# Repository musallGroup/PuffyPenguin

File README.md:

# PuffyPengiun

Multimodal rate discriminaton behavioral task for mice.

## Description of the setup

This should show a labeled picture of the setup. 

## Data saving and automatic copy

This should say what gets saved where and what is automatically copied and when. 

The TouchShaker teensy module reports lick and handle touch times, these get communicated and logged by Bpod.

### SessionData.RawEvents

Event list correspondence :

| TouchShaker byte | Event |
|------------------|-------|
| TouchShaker1_1 | left_spout_touch |
| TouchShaker1_2 | right_spout_touch |
| TouchShaker1_3 | left_spout_release |
| TouchShaker1_4 | right_spout_release |
| TouchShaker1_5 | left_handle_touch |
| TouchShaker1_6 | right_handle_touch |
| TouchShaker1_7 | both_handle_touch |
| TouchShaker1_8 | left_handle_release |
| TouchShaker1_9 | right_handle_release |
| TouchShaker1_14 | acknowledge |
| TouchShaker1_15 | error |

State list correspondence:

## Settings and description

Settings can be set from Bpod (mat files in Bpod Local/Settings).
Default settings are in SpatialSparrow.m

Settings for `training control`:

| Setting | Default | Description |
|---------|---------|-------------|
| SubjectName | | Name of the mouse |
| RewardedModality | AudioVisual |'Vision', 'Audio', Somatossensory, 'AudioVisual', 'Mixed' |
| leftRewardVolume | 2 ul | Amount of water per left reward |
| rightRewardVolume | 2 ul | Amount of water per right reward |
| AutoReward | OFF | Pre-load rewarded spout |
| TrainingMode | OFF | Move spouts to the correct side |
| autoRewardVision | 1 | Fraction of self-performed trials (Vision) |
| autoRewardAudio | 1 | Fraction of self-performed trials (Auditory) |
| autoRewardPiezo | 1 | Fraction of self-performed trials (Somatossensory) |
| autoRewardMixed | 1 | Fraction of self-performed trials (Mixed) |
| LeverSound | true | Play a sound when the mouse touches the handles |
| RegularStim | false | Produce regular stimuli sequences |
| biasSeqLength | 3 | nr of trials on one side after which the oposite side is switched with 50% probability |

Settings for `trial timing` :

| Setting | Default | Description |
|---------|---------|-------------|
| preStimDelay | 1 (s) | time on handle before stimuli presentation |
| StimDuration | 1 (s) | duration of the stimulus |
| happyTime | 0.5 (s) | duration of the last state (gives time to collect reward) |
| varStimDur | 0 (s) | variable stim duration (StimDuration + varStimDur) is the actual stim duration |
| optoDur | 0.5 (s) | duration of the optogenetics stimuli |
| optoRmp | 0.2 (s) | duration of the optogenetics ramp down (optoDur = 0.5 and optoRamp = 0.2 makes a 500ms stimulus that ramps down after 300ms) ??????? |
| minITI | 1 (s) | min inter trial interval (additional) |
| maxITI | 2 (s) | max inter trial interval (additional) |
| ITIlambda | 10 (AU) | bariability between minITI and maxITI. High lambda -> closer to minITI |
| WaitingTime | 1 (s) | minimum waiting time before a response can be made, early licks are ignored |
| TimeToChoose | 3 (s) | how long to wait for choice report |
| TimeToConfirm | 0.5 (s) | how long to wait for a 2nd (confirmation) lick |
| Timeout | 3 (s) | timeout to punish wrong responses |
| LeverWait | 10 (s) | time to wait for handle grasp |
| MoveLever | TRUE | move levers or not (set to FALSE during habituation)|
| UseBothLevers | FALSE | Whether both handles need to be touched to initiate trials |
| WaitBeforeLever | 1 (s) | Wait time before handles are moved in after trial onset|

Settings for `stimuli parameters` :

| Setting | Default | Description |
|---------|---------|-------------|
| TargRate  | 10 (Hz) | Rate of the target sequence |
| ProbRight  | 0.5 | Fraction of targets on the right |
| DistFractions  | 0  | Distractor pulses (fraction of the target sequence). Can be a scalar [0-1] or a vector |
| DistProb  | 0  | Probability of presenting a distractor |
| TestModality  | 0  | Modality to be used with discrimination (1=vis, 2=aud, 4=ss). Zero is inactive. Other values are detection only |
| BinSize  | 50 (ms) | Stimuli refractory period (min interval between pulses) |
| StimCoherence  | TRUE | Determines whether multisensory stimuli are correlated | 
| UseNoise  | FALSE | Use noise burst (TRUE) of clicks (FALSE) as auditory stimuli |
| varStimOn  | [0 0.125 0.25] (s) | Variable onset time for stimulus after lever grab in s. This can be a vector of values. Have to be 0 and higher. |
| StimGap  | 0 (s) | Duration of the gap in the middle of stimulus presentation in s; if >0 the stim duration is of stimDuration*2 + stimGap long |
| DecisionGap  | [0.3 1.5] (s) | Range of the interval between the stimulus and the decision period |
| BeepDuration  | 20 (ms) | Beep (auditory) duration |
| StimLoudness  | 0.5 | Strength of auditory stimuli |
| FlashDuration  | 20 (ms) | Flash (visual) duration |
| StimBrightness  | 20  | Brightness of flashes. Multiplier of the base frequency, default is 100Hz (????) |
| BuzzDuration  | 20 (ms) | Buzz (somatossensory) duration |
| BuzzStrength  | 1  | Strength of buzzes |
| ProbAudio  | 0  | Probability of presenting an auditory-only trial (for multimodal) |
| ProbVisual  | 0  | Probability of presenting a visual-only trial (for multimodal) |
| ProbPiezo  | 0  | Probability of presenting a somatossensory-only trial (for multimodal) |
| sRate  | 20000  | Sampling rate of the AnalogOutput module |
| PunishSoundDur  | 0 (s)  | Duration of the white noise punishment sound |
| optoProb  | 0  | Fraction of optogenetics trials |
| optoTimes  | Stimulus/Delay | Part of the trial where optogenetic stimulus should be presented |
| optoRight  | 0.5  | Probability for occurence of an optogenetic stimulus on the right |
| optoBoth  | 1  | Probability for occurence of an optogenetic stimulus on both sides. This comes after determining a single HS target ??? |
| optoPower  | 5  | Fraction of optogenetics stimuli |

Settings for `hardware control and sync` :

| Setting | Default | Description |
|---------|---------|-------------|
| SpoutSpeed | 25 (ms) | Duration of spout movement |
| rMaxSpoutIn | 30 | Right spout inner position (value between 0 and 100) |
| lMaxSpoutIn | 30 | Left spout outer position (value between 0 and 100) |
| spoutOffset | 10 | Distance from inner spout position |
| lOuterLim | 3.5 | Left spout outer position (value between 0 and 100) |
| LeverSpeed | 150 (ms) | Duration of handle movement (ms) |
| LeverIn | 20 | Inner position of the handles |
| LeverOut | 0 | Position of handle out of reach |
| TouchThresh| 5 (SDUs) | Threshold for capacitive touch lines |
| WaitForCam  | false  | Trials wait for a camera trigger to start. |

To check: rInnerLim, lInnerLim, rOuterLim, lOuterLim

Settings for `paths and data copy` :
| Setting | Default | Description |
|---------|---------|-------------|
| widefieldPath | ... | path to widefield data on server |
| serverPath |  ... | path to behavioral data on server |
| videoDrive | C: | path to behavioral data on server |
| bonsaiEXE | ... | path to bonsai.exe  |
| bonsaiParadim | ... | path to the bonsai workflow ('' to skip bonsai)  |
| labcamsAddress | localhost:9999 | address to connect to labcams for video acquisition (leave empty to skip) |
| wavePort | COM18 | COM port of the AnalogOutput Module |

`Plot` settings:
| Variable | Default | Description |
|----------|---------|-------------|
| PerformanceSwitch| Performed | Show performance over all trials or only self-performed trials |
| DoFit| false | Show curve fitting in the performance plot |
| modSelector| Combined | Which data to show in the performance plot |

Operational variables:
| Variable | Default | Description |
|----------|---------|-------------|
| SaveSettings | false | Saves the current settings |
| AdjustSpouts | 0 | Pause for spout adjustment |
| StartTime | ? | Start time of the current session |
| cTrial |  | Number of the current trial |
| runTime |  | Duration of the current session |
| servoPos | [0 0] | position of left and right spout, relative to their inner limit. these values will be changed by anti-bias correction to correct spout position |

## Instalation and build instructions

Clone the repository to Bpod Local/Protocols. If you make changes; create a branch and remember to commit changes regularly.

Build instructions coming here soon.

### Video

There are 2 options for recording video with SpatialSparrow: using [Bonsai](https://bonsai-rx.org/introduction) or using [labcams](https://bitbucket.org/jpcouto/labcams). This readme should show you how to sync the cameras to the BPod (work in progress).

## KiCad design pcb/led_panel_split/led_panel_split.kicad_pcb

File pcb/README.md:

# Printed Circuit Boards and build instructions

## Changing the printed circuit boards

The LED panel PCB was created fully in KiCAD because it is opensource. We used SeeedStudio to manufacture the circuit boards. A list of components is linked here.

### Generating gerber and drill files from KiCAD

 To get the PCB printed you may want to regenerate the GERBER and drill files.

This is how to do it to print in seeedstudio:

 - go to *File* -> *Plot*
 - select the **output directory**, plot format: **Gerber**
 - select layers: **F.Cu; B.Cu; B.SilkS;F.SilkS;B.Mask;F.Mask;Edge.Cuts**
 - select options: **Plot footprint values**; **Plot footprint references**; **Exclude PCB edge layer from other layers**; **Default line width (mm): 0.1**
 - gerber options: **Use protel filename extensions** and Format: 4.6 (unit mm)
 - clicking Plot will generate the Gerber files; to gererate drill files click *drill file*
 - Select **Merge PTH and NPTH into one file.** Unit: **milimeters** ; **suppress leading zeros** ; **PostScript** format; **Absolute origin**.

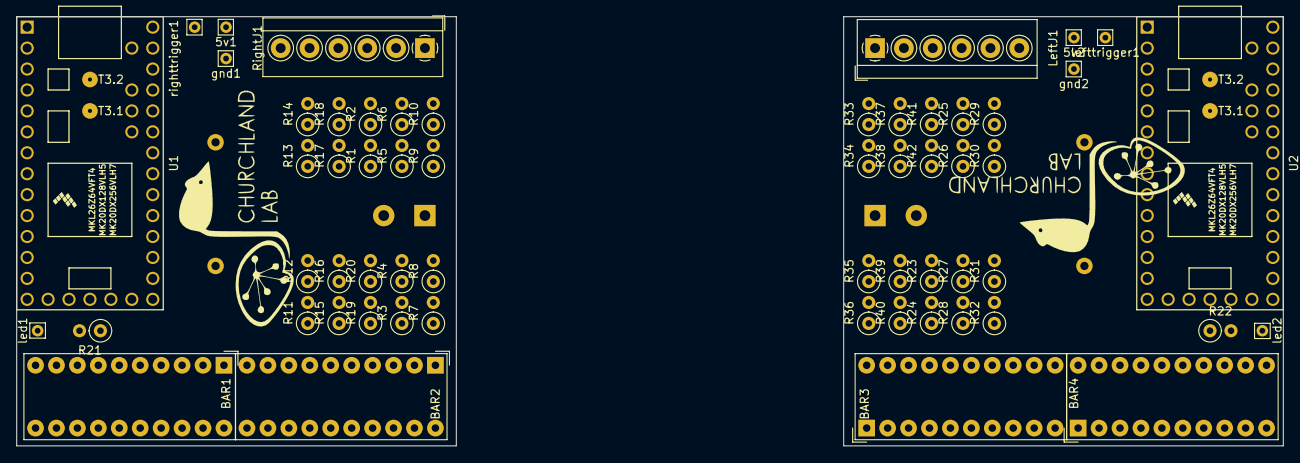
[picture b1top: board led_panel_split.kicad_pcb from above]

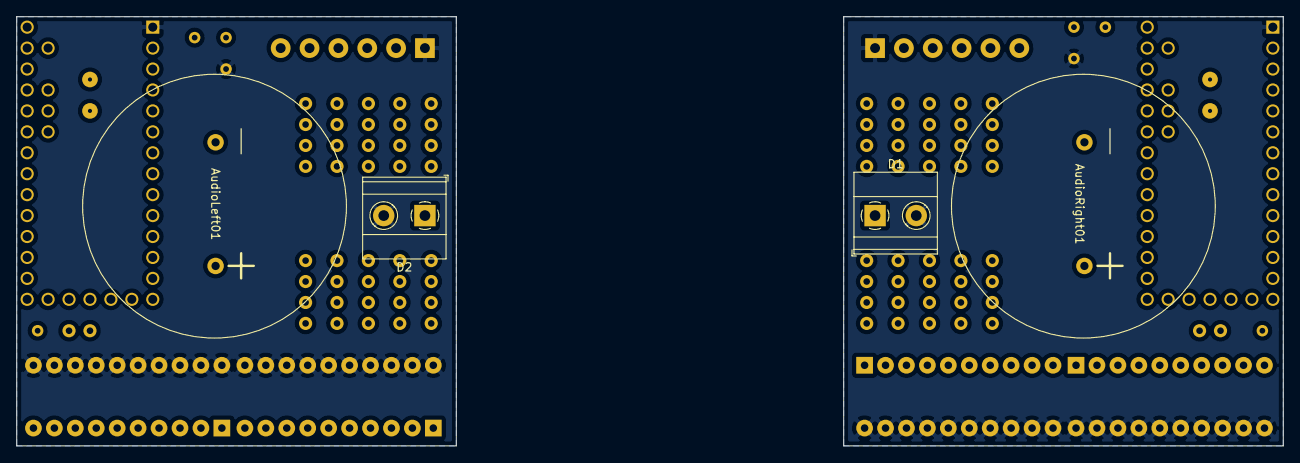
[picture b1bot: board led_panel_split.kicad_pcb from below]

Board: 2 copper layers, 153.7 x 52.1 mm, 64 parts (4 on the bottom side), 92 nets, no tracks yet.

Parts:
5v1, 5v2: 5V; Pin_D0.7mm_L6.5mm_W1.8mm_FlatFork
AudioLeft01: Audio left; speaker
AudioRight01: Audio right; speaker
BAR1, BAR2, BAR3, BAR4: HDSP-4830_2; HDSP-4830
D1, D2: LED; TerminalBlock_Phoenix_MKDS-1,5-2_1x02_P5.00mm_Horizontal
G1, G2: LOGO; churchland_lab_logo
LeftJ1: Left screw terminal; TerminalBlock_4Ucon_1x06_P3.50mm_Horizontal
R1, R2, R3, R4, R5, R6, R7, R8, R9, R10, R11, R12, R13, R14, R15, R16, R17, R18, R19, R20, R21, R22, R23, R24, R25, R26, R27, R28, R29, R30, R31, R32, R33, R34, R35, R36, R37, R38, R39, R40, R41, R42: R; R_Axial_DIN0207_L6.3mm_D2.5mm_P2.54mm_Vertical
RightJ1: Right screw terminal; TerminalBlock_4Ucon_1x06_P3.50mm_Horizontal
U1, U2: Teensy3.2; Teensy30_31_32_LC
gnd1, gnd2: GND; Pin_D0.7mm_L6.5mm_W1.8mm_FlatFork
led1: LED1 test; Pin_D0.7mm_L6.5mm_W1.8mm_FlatFork
led2: LED2 test; Pin_D0.7mm_L6.5mm_W1.8mm_FlatFork
lefttrigger1: left trigger; Pin_D0.7mm_L6.5mm_W1.8mm_FlatFork
righttrigger1: right trigger; Pin_D0.7mm_L6.5mm_W1.8mm_FlatFork

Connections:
+5V: 5v1.1, 5v2.1, LeftJ1.2, RightJ1.2, U1.33, U2.33
GND: BAR1.11, BAR1.12, BAR1.13, BAR1.14, BAR1.15, BAR1.16, BAR1.17, BAR1.18, BAR1.19, BAR1.20, BAR2.11, BAR2.12, BAR2.13, BAR2.14, BAR2.15, BAR2.16, BAR2.17, BAR2.18, BAR2.19, BAR2.20, BAR3.11, BAR3.12, BAR3.13, BAR3.14, BAR3.15, BAR3.16, BAR3.17, BAR3.18, BAR3.19, BAR3.20, BAR4.11, BAR4.12, BAR4.13, BAR4.14, BAR4.15, BAR4.16, BAR4.17, BAR4.18, BAR4.19, BAR4.20, D1.2, D2.2, LeftJ1.1, RightJ1.1, U1.1, U2.1, gnd1.1, gnd2.1
unnamed: AudioLeft01.1, LeftJ1.5
unnamed: AudioLeft01.2, LeftJ1.6
unnamed: AudioRight01.1, RightJ1.5
unnamed: AudioRight01.2, RightJ1.6
unnamed: BAR1.1, R20.2
unnamed: BAR1.2, R19.2
unnamed: BAR1.3, R18.2
unnamed: BAR1.4, R17.2
unnamed: BAR1.5, R16.2
unnamed: BAR1.6, R15.2
unnamed: BAR1.7, R14.2
unnamed: BAR1.8, R13.2
unnamed: BAR1.9, R12.2
unnamed: BAR1.10, R11.2
unnamed: BAR2.1, R10.2
unnamed: BAR2.2, R9.2
unnamed: BAR2.3, R8.2
unnamed: BAR2.4, R7.2
unnamed: BAR2.5, R6.2
unnamed: BAR2.6, R5.2
unnamed: BAR2.7, R4.2
unnamed: BAR2.8, R3.2
unnamed: BAR2.9, R2.2
unnamed: BAR2.10, R1.2
unnamed: BAR3.1, R33.2
unnamed: BAR3.2, R34.2
unnamed: BAR3.3, R35.2
unnamed: BAR3.4, R36.2
unnamed: BAR3.5, R37.2
unnamed: BAR3.6, R38.2
unnamed: BAR3.7, R39.2
unnamed: BAR3.8, R40.2
unnamed: BAR3.9, R41.2
unnamed: BAR3.10, R42.2
unnamed: BAR4.1, R23.2
unnamed: BAR4.2, R24.2
unnamed: BAR4.3, R25.2
unnamed: BAR4.4, R26.2
unnamed: BAR4.5, R27.2
unnamed: BAR4.6, R28.2
unnamed: BAR4.7, R29.2
unnamed: BAR4.8, R30.2
unnamed: BAR4.9, R31.2
unnamed: BAR4.10, R32.2
unnamed: D1.1, R21.2
unnamed: D2.1, R22.2
unnamed: LeftJ1.3, R22.1, led2.1
unnamed: LeftJ1.4, U2.30, lefttrigger1.1
unnamed: R1.1, U1.12
unnamed: R2.1, U1.13
unnamed: R3.1, U1.14
unnamed: R4.1, U1.20
unnamed: R5.1, U1.21
unnamed: R6.1, U1.22
unnamed: R7.1, U1.23
unnamed: R8.1, U1.24
unnamed: R9.1, U1.25
unnamed: R10.1, U1.26
unnamed: R11.1, U1.2
unnamed: R12.1, U1.3
unnamed: R13.1, U1.4
unnamed: R14.1, U1.5
unnamed: R15.1, U1.6
unnamed: R16.1, U1.7
unnamed: R17.1, U1.8
unnamed: R18.1, U1.9
unnamed: R19.1, U1.10
unnamed: R20.1, U1.11
unnamed: R21.1, RightJ1.3, led1.1
unnamed: R23.1, U2.11
unnamed: R24.1, U2.10
unnamed: R25.1, U2.9
unnamed: R26.1, U2.8
unnamed: R27.1, U2.7
unnamed: R28.1, U2.6
unnamed: R29.1, U2.5
unnamed: R30.1, U2.4
unnamed: R31.1, U2.3
unnamed: R32.1, U2.2
unnamed: R33.1, U2.26
unnamed: R34.1, U2.25
unnamed: R35.1, U2.24
unnamed: R36.1, U2.23
unnamed: R37.1, U2.22
unnamed: R38.1, U2.21
unnamed: R39.1, U2.20
unnamed: R40.1, U2.14
unnamed: R41.1, U2.13
unnamed: R42.1, U2.12
unnamed: RightJ1.4, U1.30, righttrigger1.1

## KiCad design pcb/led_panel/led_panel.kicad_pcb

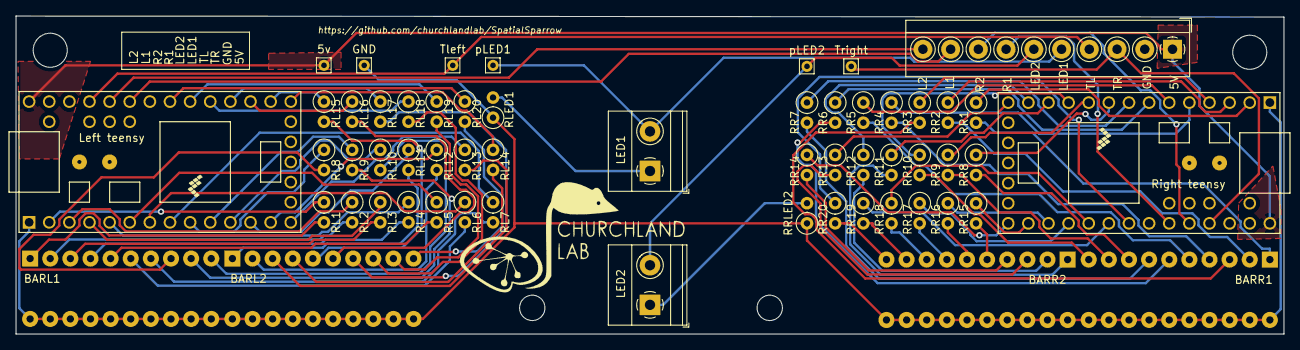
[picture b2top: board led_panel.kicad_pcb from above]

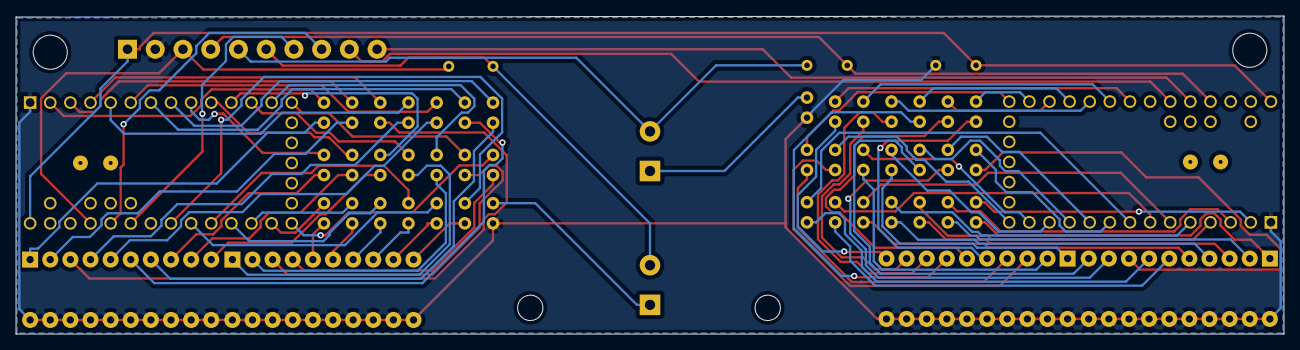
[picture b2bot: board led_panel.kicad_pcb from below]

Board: 2 copper layers, 160.0 x 40.1 mm, 61 parts (2 on the bottom side), 92 nets.

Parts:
5v: 5V; Pin_D0.7mm_L6.5mm_W1.8mm_FlatFork
BARL1, BARL2: HDSP-4830_2; HDSP-4830
BARR1, BARR2: HDSP-4830_2; HDSP-4830
GND: GND; Pin_D0.7mm_L6.5mm_W1.8mm_FlatFork
LED1, LED2: LED; TerminalBlock_Phoenix_MKDS-1,5-2_1x02_P5.00mm_Horizontal
Left teensy: Teensy3.2; Teensy30_31_32_LC
M3_1, M3_2: MountingHole_3.2mm_M3
M4_1, M4_2: MountingHole_4.3mm_M4
RL1, RL2, RL3, RL4, RL5, RL6, RL7, RL8, RL9, RL10, RL11, RL12, RL13, RL14, RL15, RL16, RL17, RL18, RL19, RL20: R; R_Axial_DIN0207_L6.3mm_D2.5mm_P2.54mm_Vertical
RLED1: R; R_Axial_DIN0207_L6.3mm_D2.5mm_P2.54mm_Vertical
RR1, RR2, RR3, RR4, RR5, RR6, RR7, RR8, RR9, RR10, RR11, RR12, RR13, RR14, RR15, RR16, RR17, RR18, RR19, RR20: R; R_Axial_DIN0207_L6.3mm_D2.5mm_P2.54mm_Vertical
RRLED2: R; R_Axial_DIN0207_L6.3mm_D2.5mm_P2.54mm_Vertical
Right teensy: Teensy3.2; Teensy30_31_32_LC
Tleft: T right; Pin_D0.7mm_L6.5mm_W1.8mm_FlatFork
Tright: T right; Pin_D0.7mm_L6.5mm_W1.8mm_FlatFork
pLED1: LED1; Pin_D0.7mm_L6.5mm_W1.8mm_FlatFork
pLED2: LED2; Pin_D0.7mm_L6.5mm_W1.8mm_FlatFork
terminal: Screw_Terminal_01x10; TerminalBlock_4Ucon_1x10_P3.50mm_Horizontal

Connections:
+5V: 5v.1, Left teensy.33, Right teensy.33, terminal.1
GND: BARL1.11, BARL1.12, BARL1.13, BARL1.14, BARL1.15, BARL1.16, BARL1.17, BARL1.18, BARL1.19, BARL1.20, BARL2.11, BARL2.12, BARL2.13, BARL2.14, BARL2.15, BARL2.16, BARL2.17, BARL2.18, BARL2.19, BARL2.20, BARR1.11, BARR1.12, BARR1.13, BARR1.14, BARR1.15, BARR1.16, BARR1.17, BARR1.18, BARR1.19, BARR1.20, BARR2.11, BARR2.12, BARR2.13, BARR2.14, BARR2.15, BARR2.16, BARR2.17, BARR2.18, BARR2.19, BARR2.20, GND.1, Left teensy.1, RLED1.1, RRLED2.1, Right teensy.1, terminal.2
unnamed: BARL1.1, RL1.2
unnamed: BARL1.2, RL2.2
unnamed: BARL1.3, RL3.2
unnamed: BARL1.4, RL4.2
unnamed: BARL1.5, RL5.2
unnamed: BARL1.6, RL6.2
unnamed: BARL1.7, RL7.2
unnamed: BARL1.8, RL8.2
unnamed: BARL1.9, RL9.2
unnamed: BARL1.10, RL10.2
unnamed: BARL2.1, RL11.2
unnamed: BARL2.2, RL12.2
unnamed: BARL2.3, RL13.2
unnamed: BARL2.4, RL14.2
unnamed: BARL2.5, RL15.2
unnamed: BARL2.6, RL16.2
unnamed: BARL2.7, RL17.2
unnamed: BARL2.8, RL18.2
unnamed: BARL2.9, RL19.2
unnamed: BARL2.10, RL20.2
unnamed: BARR1.1, RR1.2
unnamed: BARR1.2, RR2.2
unnamed: BARR1.3, RR3.2
unnamed: BARR1.4, RR4.2
unnamed: BARR1.5, RR5.2
unnamed: BARR1.6, RR6.2
unnamed: BARR1.7, RR7.2
unnamed: BARR1.8, RR8.2
unnamed: BARR1.9, RR9.2
unnamed: BARR1.10, RR10.2
unnamed: BARR2.1, RR11.2
unnamed: BARR2.2, RR12.2
unnamed: BARR2.3, RR13.2
unnamed: BARR2.4, RR14.2
unnamed: BARR2.5, RR15.2
unnamed: BARR2.6, RR16.2
unnamed: BARR2.7, RR17.2
unnamed: BARR2.8, RR18.2
unnamed: BARR2.9, RR19.2
unnamed: BARR2.10, RR20.2
unnamed: LED1.1, RLED1.2
unnamed: LED1.2, pLED1.1, terminal.5
unnamed: LED2.1, RRLED2.2
unnamed: LED2.2, pLED2.1, terminal.6
unnamed: Right teensy.30, Tright.1, terminal.3
unnamed: Left teensy.30, Tleft.1, terminal.4
unnamed: Right teensy.28, terminal.7
unnamed: Right teensy.29, terminal.8
unnamed: Left teensy.28, terminal.9
unnamed: Left teensy.29, terminal.10
unnamed: Left teensy.2, RL1.1
unnamed: Left teensy.3, RL2.1
unnamed: Left teensy.4, RL3.1
unnamed: Left teensy.5, RL4.1
unnamed: Left teensy.6, RL5.1
unnamed: Left teensy.7, RL6.1
unnamed: Left teensy.8, RL7.1
unnamed: Left teensy.9, RL8.1
unnamed: Left teensy.10, RL9.1
unnamed: Left teensy.11, RL10.1
unnamed: Left teensy.13, RL12.1
unnamed: Left teensy.14, RL13.1
unnamed: Left teensy.20, RL14.1
unnamed: Left teensy.21, RL15.1
unnamed: Left teensy.22, RL16.1
unnamed: Left teensy.23, RL17.1
unnamed: Left teensy.24, RL18.1
unnamed: Left teensy.25, RL19.1
unnamed: Left teensy.26, RL20.1
unnamed: RR1.1, Right teensy.2
unnamed: RR2.1, Right teensy.3
unnamed: RR3.1, Right teensy.4
unnamed: RR4.1, Right teensy.5
unnamed: RR5.1, Right teensy.6
unnamed: RR6.1, Right teensy.7
unnamed: RR7.1, Right teensy.8
unnamed: RR8.1, Right teensy.9
unnamed: RR9.1, Right teensy.10
unnamed: RR10.1, Right teensy.11
unnamed: RR11.1, Right teensy.12
unnamed: RR12.1, Right teensy.13
unnamed: RR13.1, Right teensy.14
unnamed: RR14.1, Right teensy.20
unnamed: RR15.1, Right teensy.21
unnamed: RR16.1, Right teensy.22
unnamed: RR17.1, Right teensy.23
unnamed: RR18.1, Right teensy.24
unnamed: RR19.1, Right teensy.25
unnamed: RR20.1, Right teensy.26
unnamed: Left teensy.12, RL11.1

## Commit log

2021-09-21 added first puffy pengiun functions for stimulus generation
2021-10-09 first working version
2021-10-10 some updates for usabiliy
2021-10-10 fixed bug with timing of the tactile stimulus sequence
2021-10-20 bunch of updates for usability. Started collecting 2p data with this.
2021-11-01 some bug fixes to adjust touch thresholds
2021-11-02 updates for stability and showing trial performance
2021-11-02 some minor updates
2021-11-03 fixed trial performance plot
2021-11-29 updates to show trial history
2022-01-30 added short code to plot learning curve for current animal at the end of each session
2022-03-07 some updates to show mdality performance
2022-04-03 added correction for case with equal amount of stimuli on both sides
2022-05-13 added some parts
2022-05-27 latest version from 2p setup. Used for new build
2022-05-31 fixed teensywrite bug
2022-06-10 added behavioral analysis code for innate task
2022-06-10 small update to innate analysis
2022-06-10 moved analysis files
2022-06-13 added trial numbers to plot
2022-06-15 Screws for order
2022-07-28 added some code for behavioral analysis
2022-07-28 added code to compute performance at different optogenetic power levels in auditory task
2022-10-24 iPad monitor clamps
2022-10-25 Increased tube diameter for airpuffs
    This should be easier for the 3D print
2022-10-28 analysis updates
2022-10-28 more parts
2023-01-31 updated version from working setup. Includes sequential optogenetic trials
2023-01-31 changed 'AllMixed' to shuffle all multisensory conditions
    Stopped main GUI to be brought to foreground in every trial
2023-03-09 Moved old assembly parts for clarity
2023-03-09 updated spout assembly with larger tubes and side screws for camera
2023-03-21 added optoSeq functionality
2023-03-21 small updates to visual stimulator
2023-03-21 minor changes from new setup. fixed issue with not updating module ports when rediscovered in the beginning.
2023-03-22 UV lamp- water valves
2023-03-30 small update to separate sides of optogenetics with eopn3
2023-03-31 small updates
2023-04-12 Updated the Airpuff Spout assembly
    I was afraid of puffing the animal in the face and aimed the Airpuffs a bit further out. This turned out to have been to far away and I needed to aim the air a bit closer to the face after all.
2023-04-12 Updated water spout adapters
    We use a new version of water spouts now that have a larger diameter. In some cases this caused issues with fitting into the old version of the spout holders. I increased the space for the spout now.
2023-04-14 Updated drawings for the boxes
2023-04-18 Create 2p-PT-holder.stl
    Phototransistor holder design for 2p monitor
2023-04-24 Updated plugs
2023-04-24 boxs
    boxs
2023-04-27 New design for boxes added
2023-05-15 more updates to setup function for multisensory discrimination
2023-05-19 corrected bug for discrimination loop and fixed GUI window
2023-06-08 update to ITI scaling
2023-08-01 added improved COM search routine
2023-08-07 minor bug fix and update for compatibility with new labcams
2023-12-26 added hardware reset option for teensyhaker. should reset by default at session start.
2023-12-28 added code to talk to laser gate module
2024-02-23 Updated StepperToSpout
2024-02-23 Revert "Merge branch 'main' of https://github.com/musallGroup/PuffyPenguin"
    This reverts commit 3fa0c4bc5f0a0f098de540fe23160a26a2d1d6f4, reversing
    changes made to 0ac26d5963956c4db7cf7d0fba36031d2f8736f7.
2024-02-28 widefield setup at FZJ
2024-03-26 Reinforced StepperToSpout
2024-03-26 Updated annotations on prints for better IRL Version control
2024-03-26 moved outdated parts to backup
2024-04-13 Breakout PCB added
2024-05-16 restored LaserGate teensy code
2024-05-16 added LEDramper to teensy code
2024-06-30 added wheel parts
2024-10-24 updated some parts to include pinch valves in water holder
2025-04-30 added new discrimination version
    This is based on the code on CMP391 - the setup that was used for photometry measurements in the striatal learning project
2025-07-15 added headbar holders
2025-11-21 teensy updates for 4.0
2026-05-01 Pushed updated version from local PC CMP323 (2photon behavior PC)
    Updates are references in the file PuffyPenguin_directory_comparison.txt
2026-05-01 Pushed version from CMP321 (widefield behavior PC at FZJ)
    Will have to check how different versions compare with the code from 323 and create an updated merge next
2026-05-01 merged version. Mostly using the settings from the 2p behavioral setup but GUI code from the widefield.
2026-05-01 Update PuffyPenguin_AutoReward.m
    Now includes triggering single spout trials on the ignored if animals are strongly biased in the last 10 trials
2026-05-01 added function for auditory warning if the behavior is off
